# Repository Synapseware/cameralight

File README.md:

cameralight
===========

## About
The camera light is meant to be just that - a camera light.  But with a twist: It's meant to be an underwater lighting platform using a ring of white LEDs around the camera lens housing (which is probably a really bad idea in practice).  The module uses a LIPO battery, inductive charging and photo sensors to turn on and off.  It has very low power draw when "off" allowing it to stay in standby mode for quite a long time.  The only other "complex" part of the circuit is a boost-mode constant current LED driver, which is supposed to light up those LEDs enough to actually work underwater.  But who wants to go diving at night?

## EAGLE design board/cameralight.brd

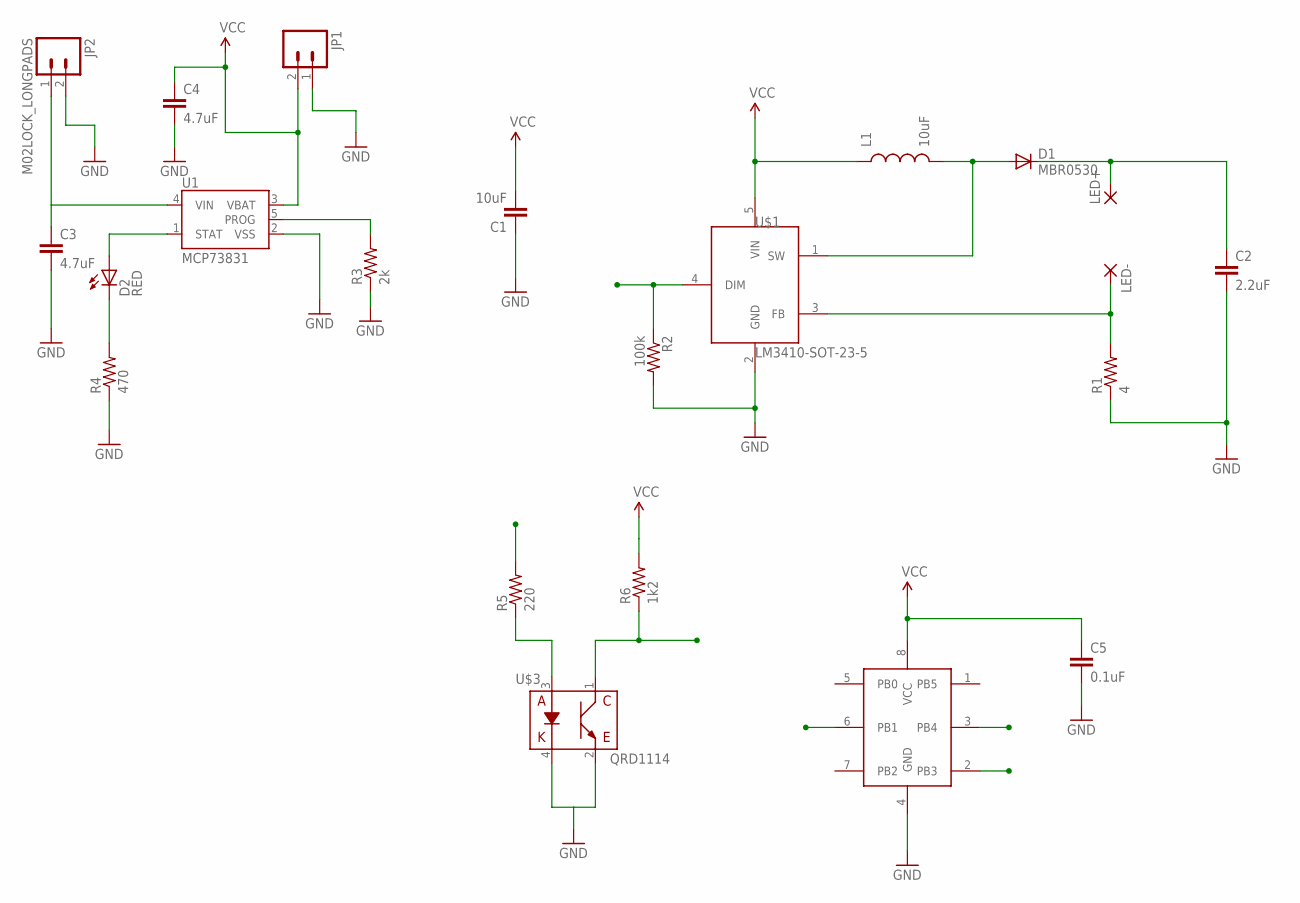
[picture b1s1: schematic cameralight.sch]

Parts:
C1: 10uF; CTZ3
C2: 2.2uF; CTZ3
C3, C4: 4.7uF; 1206
C5: 0.1uF; 0603-CAP
D1: MBR0530; SOD123
D2: RED; LED-0603
JP1: M02-JST-2MM-SMT; JST-2-SMD
JP2: M02LOCK_LONGPADS; 1X02_LOCK_LONGPADS
L1: 10uF; CR54
LED+: 2,54/1,0
LED-: 2,54/1,0
R1: 4; 0603-RES
R2: 100k; 0603-RES
R3: 2k; 1206
R4: 470; 0603-RES
R5: 220; 0603-RES
R6: 1k2; 0603-RES
U1: MCP73831; SOT23-5
U$1: LM3410-SOT-23-5; SOT-23-5
U$2: ATTINY13; WSOIC-8
U$3: QRD1114

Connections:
DIM: R2.1, U$1.4 (DIM), U$2.6 (PB1)
GND: C1.+ (1), C2.- (2), C3.2, C4.2, C5.2, JP1.1 (2), JP2.2, R1.1, R2.2, R3.1, R4.1, U1.2 (VSS), U$1.2 (GND), U$2.4 (GND), U$3.2 (C), U$3.4 (K)
LED+: C2.+ (1), D1.C, LED+.1
LED-: LED-.1, R1.2, U$1.3 (FB)
unnamed: D1.A, L1.P$2 (2), U$1.1 (SW)
unnamed: R3.2, U1.5 (PROG)
unnamed: D2.A, U1.1 (STAT)
unnamed: D2.C, R4.2
unnamed: C3.1, JP2.1, U1.4 (VIN)
unnamed: R5.1, U$3.3 (A)
PROX_EN: R5.2, U$2.2 (PB3)
PROX_SNS: R6.1, U$2.3 (PB4), U$3.1 (E)
VCC: C1.- (2), C4.1, C5.1, JP1.2 (1), L1.P$1 (1), R6.2, U1.3 (VBAT), U$1.5 (VIN), U$2.8 (VCC)

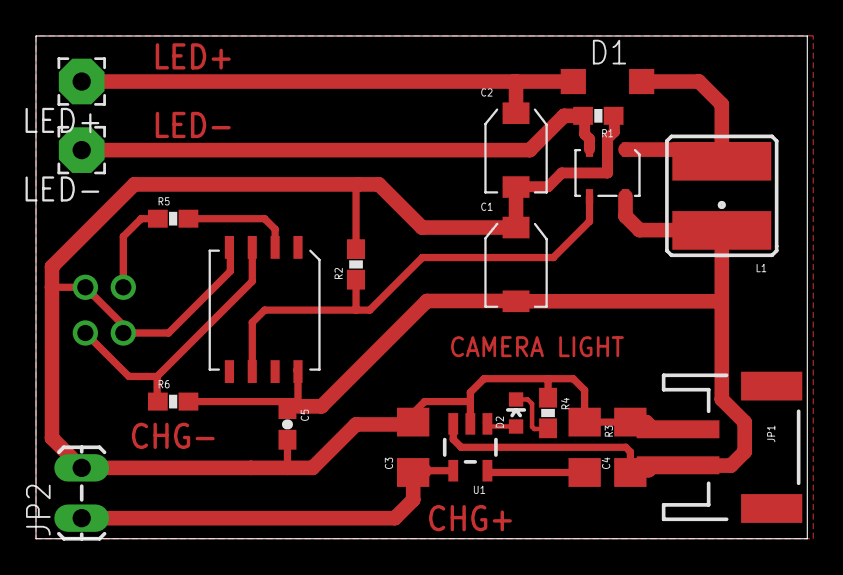
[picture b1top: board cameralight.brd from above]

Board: 2 copper layers, 42.9 x 27.9 mm, 22 parts (1 on the bottom side), 13 nets.

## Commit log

2014-06-06 Adding libs and updating make
2014-09-29 renaming makefile

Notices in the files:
parts and their libraries:
SparkFun-Passives: Licensing: CC v3.0 Share-Alike You are welcome to use this library for commercial purposes.
